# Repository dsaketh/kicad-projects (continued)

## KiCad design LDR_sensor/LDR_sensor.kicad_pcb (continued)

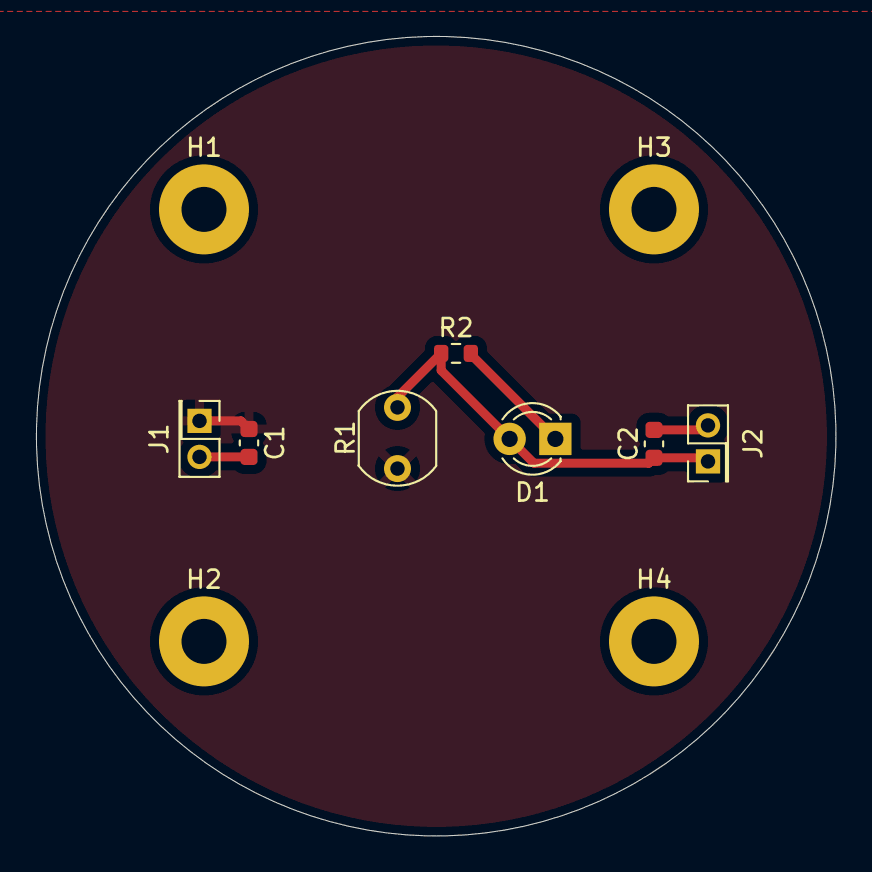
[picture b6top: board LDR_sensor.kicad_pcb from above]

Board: 2 copper layers, 44.4 x 44.4 mm, 11 parts (0 on the bottom side), 3 nets.

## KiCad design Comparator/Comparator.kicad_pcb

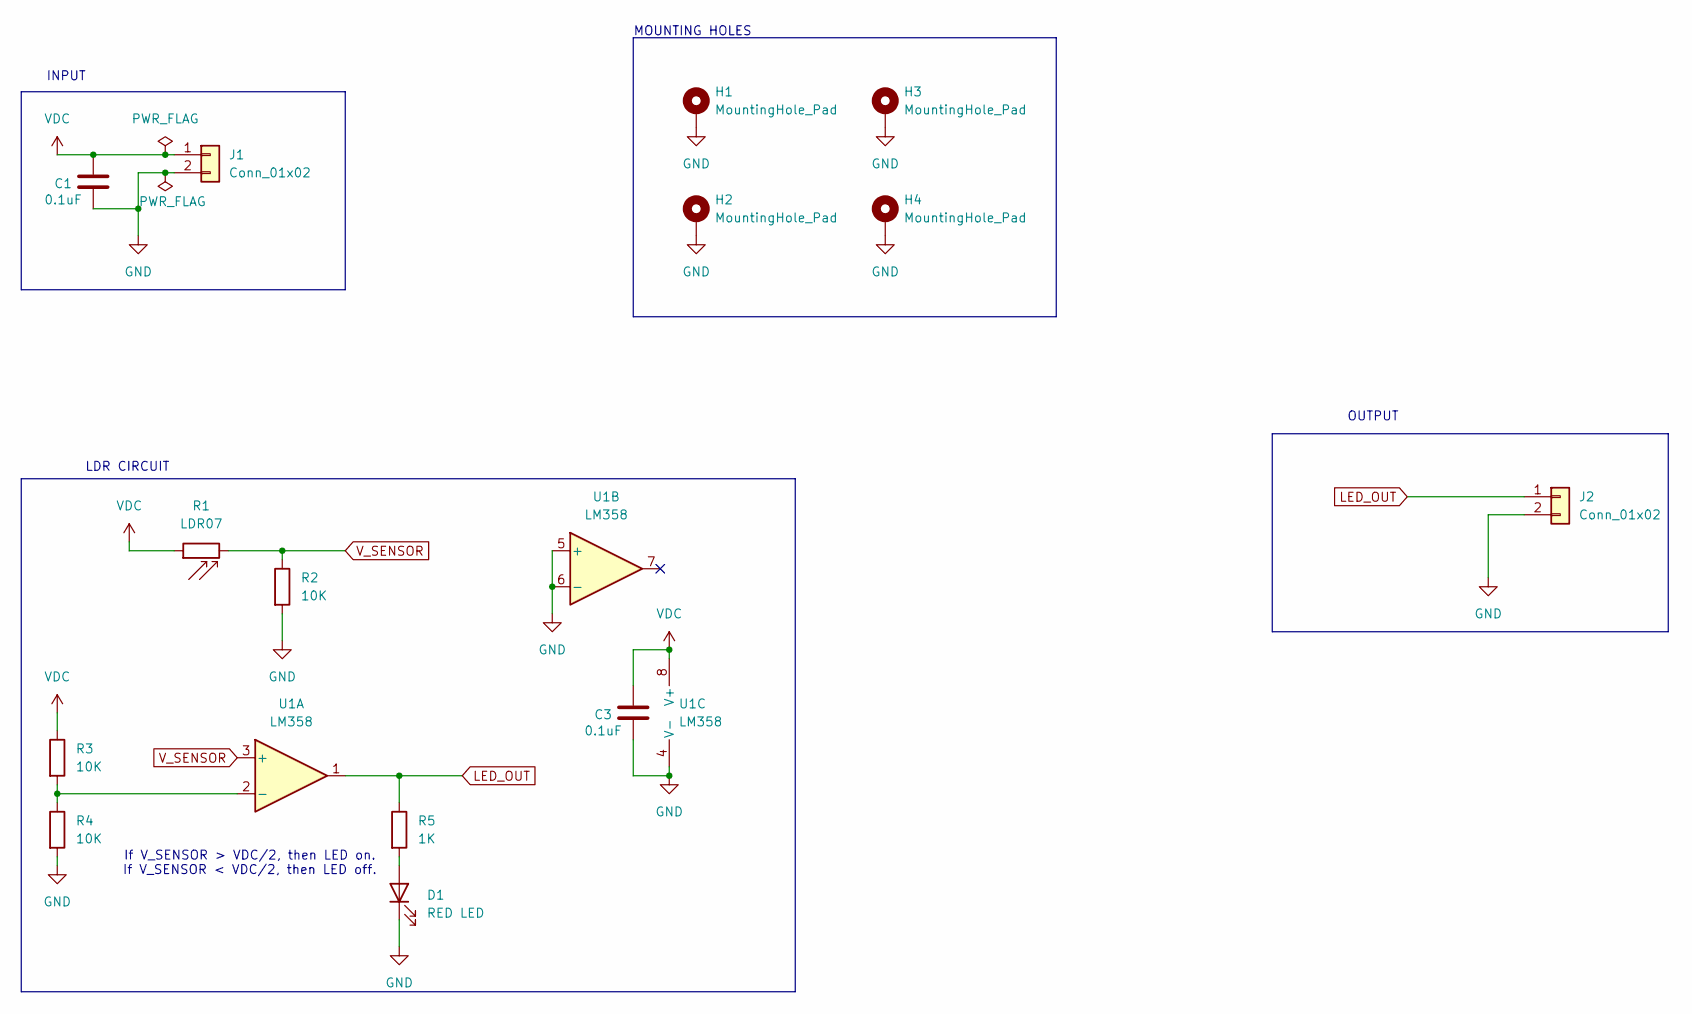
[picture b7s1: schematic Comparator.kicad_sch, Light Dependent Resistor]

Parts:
C1, C3: 0.1uF; C_0603_1608Metric
D1: RED LED; LED_D3.0mm
H1, H2, H3, H4: MountingHole_Pad; MountingHole_2.5mm_Pad
J1, J2: Conn_01x02; PinHeader_2x01_P2.00mm_Vertical
R1: LDR07; R_LDR_5.1x4.3mm_P3.4mm_Vertical
R2, R3, R4: 10K; R_0603_1608Metric
R5: 1K; R_0603_1608Metric
U1: LM358; SOIC-8_3.9x4.9mm_P1.27mm

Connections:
GND: C1.2, C3.2, D1.1 (K), H1.1, H2.1, H3.1, H4.1, J1.2, J2.2, R2.2, R4.2, U1.4 (V-), U1.5 (+), U1.6 (-)
LED_OUT: J2.1, R5.1, U1.1
unnamed: D1.2 (A), R5.2
unnamed: R3.2, R4.1, U1.2 (-)
VDC: C1.1, C3.1, J1.1, R1.1, R3.1, U1.8 (V+)
V_SENSOR: R1.2, R2.1, U1.3 (+)

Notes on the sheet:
If V_SENSOR > VDC/2, then LED on. If V_SENSOR < VDC/2, then LED off.
INPUT
LDR CIRCUIT
MOUNTING HOLES
OUTPUT

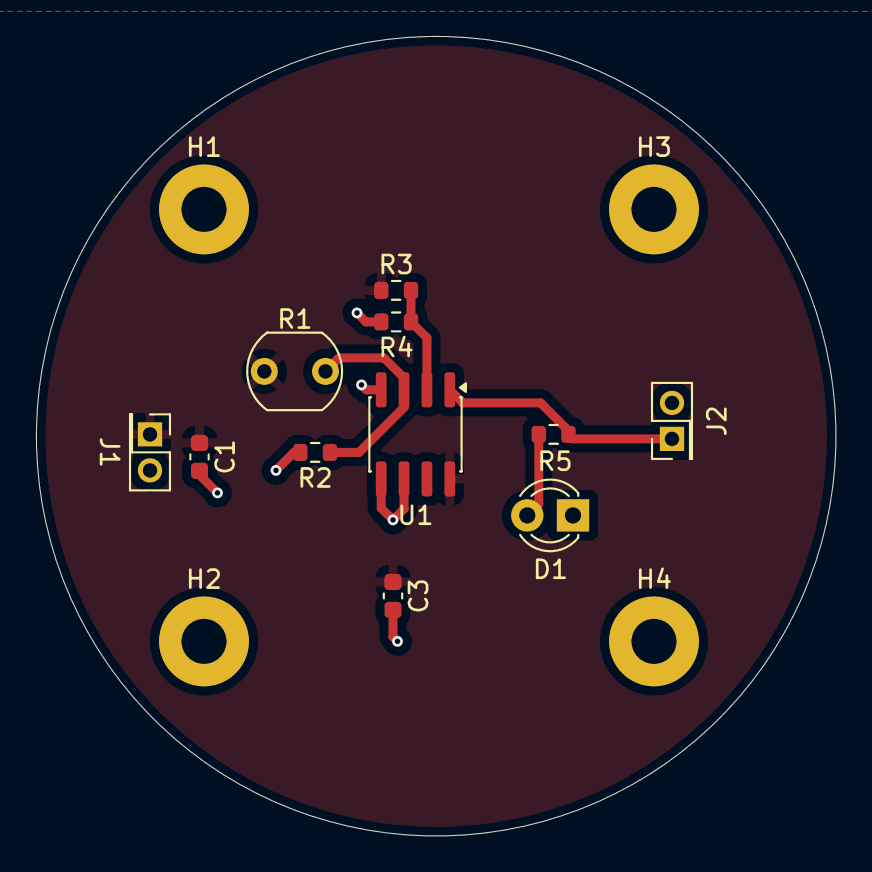
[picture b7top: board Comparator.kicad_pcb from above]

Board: 2 copper layers, 44.4 x 44.4 mm, 15 parts (0 on the bottom side), 6 nets.

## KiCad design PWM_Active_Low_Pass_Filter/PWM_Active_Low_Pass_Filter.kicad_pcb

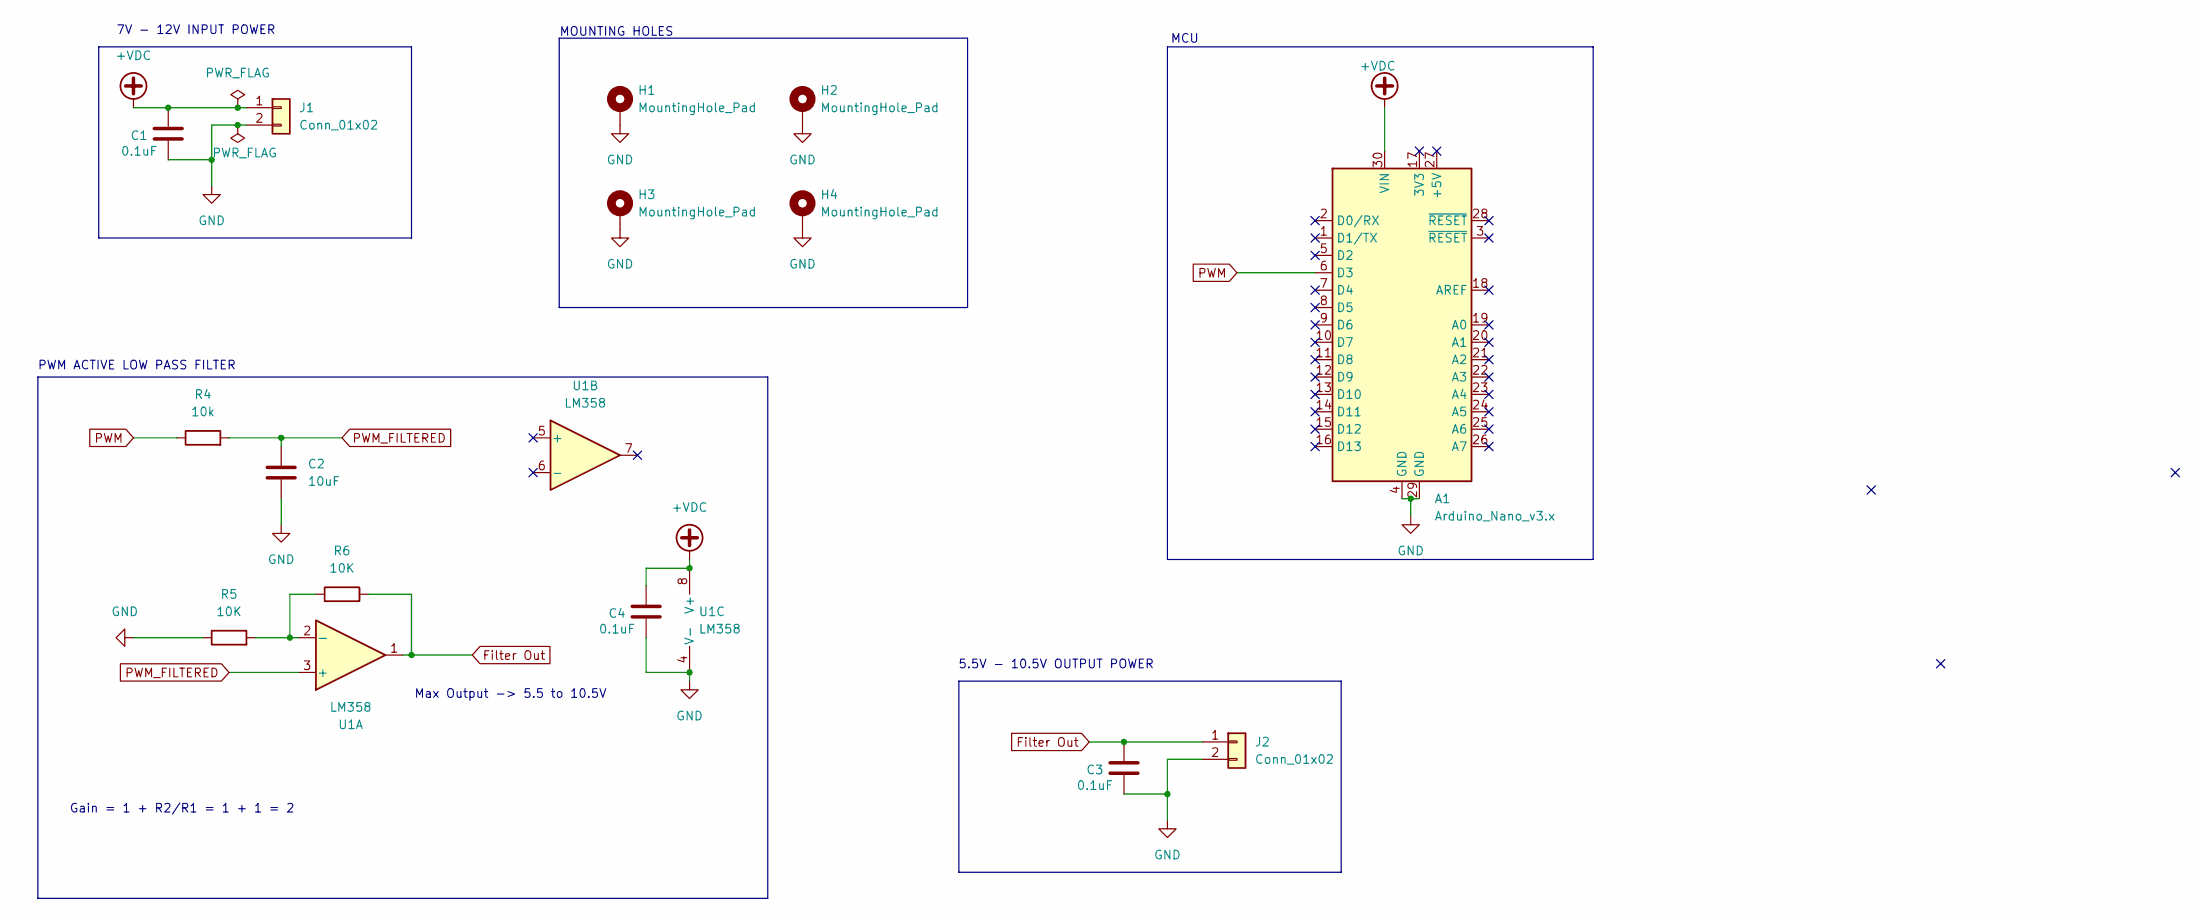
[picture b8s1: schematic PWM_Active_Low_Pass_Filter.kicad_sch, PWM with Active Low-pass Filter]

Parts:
A1: Arduino_Nano_v3.x; Arduino_Nano
C1, C3, C4: 0.1uF; C_0603_1608Metric
C2: 10uF; C_0603_1608Metric
H1, H2, H3, H4: MountingHole_Pad; MountingHole_2.5mm_Pad
J1, J2: Conn_01x02; PinHeader_2x01_P2.00mm_Vertical
R4: 10k; R_0603_1608Metric
R5: 10K; R_0603_1608Metric_Pad0.98x0.95mm_HandSolder
R6: 10K; R_0603_1608Metric
U1: LM358; SOIC-8_3.9x4.9mm_P1.27mm

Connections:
+VDC: A1.30 (VIN), C1.1, C4.1, J1.1, U1.8 (V+)
Filter Out: C3.1, J2.1, R6.2, U1.1
GND: A1.4 (GND), A1.29 (GND), C1.2, C2.2, C3.2, C4.2, H1.1, H2.1, H3.1, H4.1, J1.2, J2.2, R5.1, U1.4 (V-)
unnamed: R5.2, R6.1, U1.2 (-)
PWM: A1.6 (D3), R4.1
PWM_FILTERED: C2.1, R4.2, U1.3 (+)

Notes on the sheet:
5.5V - 10.5V OUTPUT POWER
MCU
MOUNTING HOLES
Gain = 1 + R2/R1 = 1 + 1 = 2
Max Output -> 5.5 to 10.5V
PWM ACTIVE LOW PASS FILTER
7V - 12V INPUT POWER

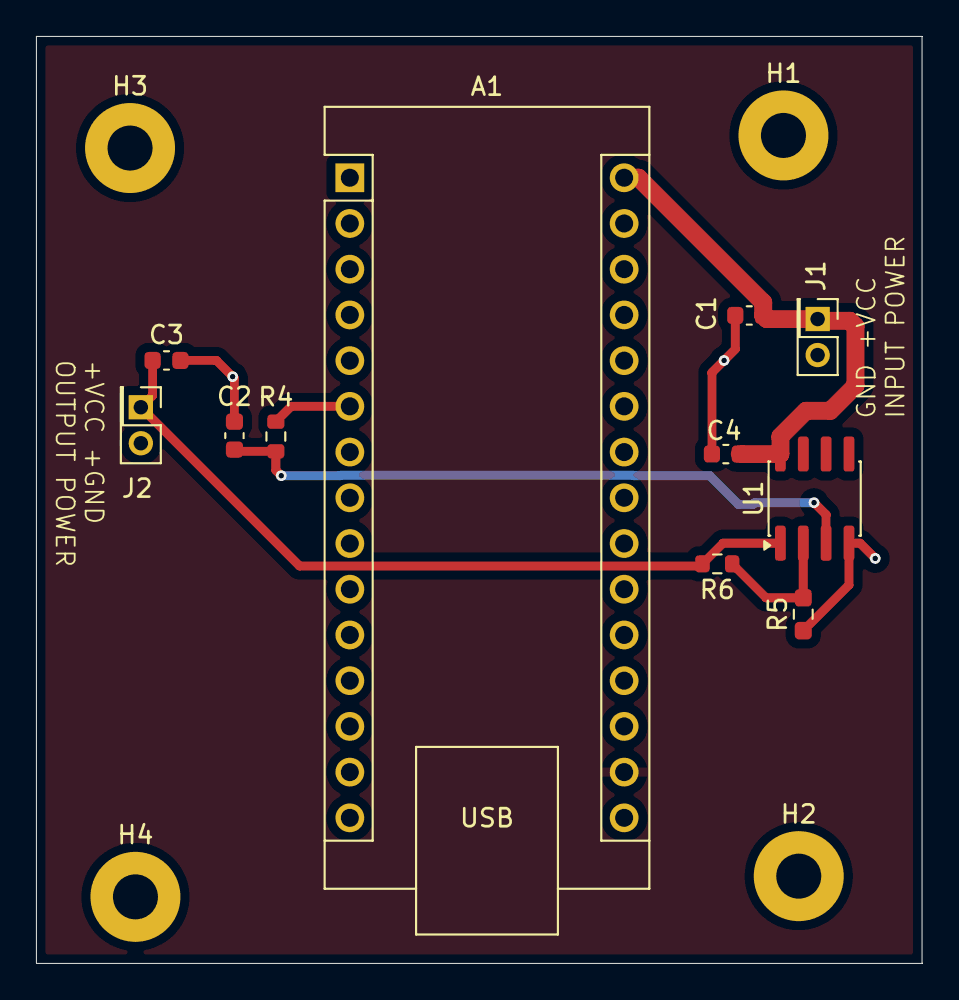
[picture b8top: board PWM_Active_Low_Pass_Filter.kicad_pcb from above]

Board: 2 copper layers, 49.2 x 51.5 mm, 15 parts (0 on the bottom side), 6 nets.

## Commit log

2026-03-21 Initial Commit: added KiCad projects
2026-03-21 Added Text box
    Added a text box around MOSFET Push Button Circuitry
2026-03-21 Delete Duplicate Project
    Deleted LED_Transistor because it is a duplicate of LED_MOSFET_BUTTON
2026-03-21 Added Project Schematic PDFs
    For each KiCad project, a schematic pdf was generated.
2026-03-21 New Project File
    PWM with Active Low Pass Filter Project File
2026-03-21 NO Change
2026-03-22 File clean up
2026-03-22 Output Power text block update
2026-03-27 Add LDR and Comparator Projects
2026-03-27 added LDR and comparator project descriptions
2026-03-29 Add Voltage Regulator project, update PWM Active Low Project
2026-03-29 Updated Schematic Sheet Info and added PDF
2026-03-29 Update Schematic and add PDF
2026-04-01 Add 555 Timer LED Blink Project
2026-04-02 Add Temp Sensor Project
2026-04-03 Updated Temperature Sensor Project
    - Added Raspberry Pi Pico
    - I2C Connector
    - UART Connector
    - Reset Pushbutton
2026-04-05 Update Temperature Sensor
    - added 0.1 uF capacitors to VBUS and VSYS
    - Changed board stack up from 2 layer to a 4 layer for flexibility on routing and better organization
2026-04-05 Updated Temperature Sensor PCB Layout
    - Removed Power Plane cut for 3.3V and dedicated an inner plane for 3.3V.
    - Added connections for 3.3V SMD components
2026-04-05 Update Temperature Sensor Project
2026-04-12 Add Embedded Sensor Platform Project
    - I2C, UART
    - Raspberry PI Pico
    - LM35 Temperature Sensor
    - SSD1306 OLED I2C Display
2026-04-12 Update Embedded Sensor Platform (RP2040)
    - Changed pin assignment of I2C connector to be [GND, VCC, SCL, SDA]
    - Removed I2C OLED Display footprint and replaced with generic 4-pin vertical connector for flexibility.
2026-04-18 Update Embedded Sensor Project
    - Removed additional I2C connector
    - Adjusted I2C OLED Display Placement
    - Adjusted UART Connector Placement
    - Adjustment Board Dimensions
    - Changed GPIO Assignments for Interfaces on MCU for improved part placement
2026-04-19 Add RP2040 Custom Board
